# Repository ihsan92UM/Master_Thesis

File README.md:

# Master_Thesis

## Repository Structure
```
Master_Thesis/
├── graphics/
│   └── Contains all .png images used in markdown files
├── pcb_design_files/
│   └── Contains KiCAD 9.0 files 
├── programming_guides/
│   └── Contains programming setup and code import guide
├── stm32c0_codes/
    └── Demo code for funtional board incl. USB, I2C.
```

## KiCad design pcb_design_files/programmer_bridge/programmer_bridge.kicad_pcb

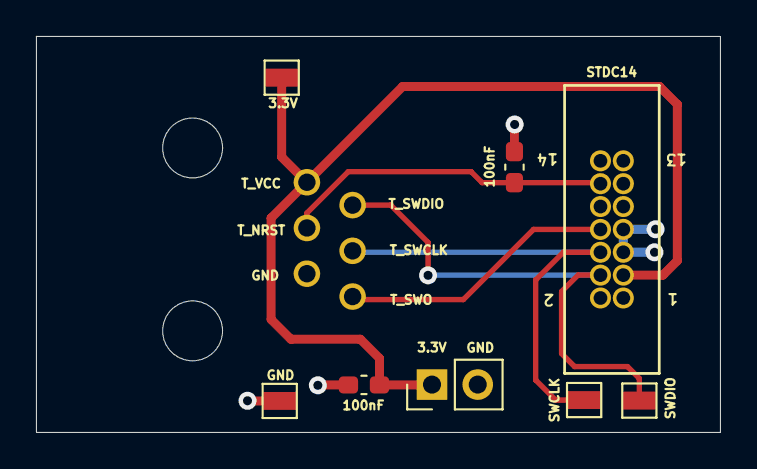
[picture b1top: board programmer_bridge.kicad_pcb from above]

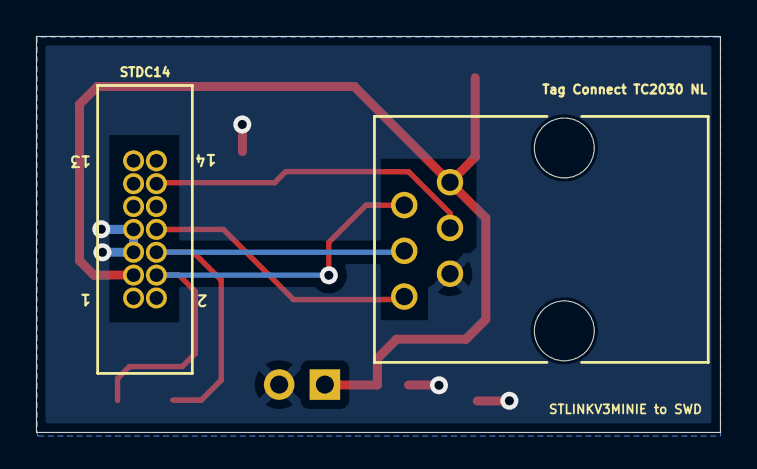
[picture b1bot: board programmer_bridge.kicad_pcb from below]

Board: 2 copper layers, 38.0 x 22.0 mm, 9 parts (2 on the bottom side), 6 nets.

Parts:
C4, C5: 100nF; C_0603_1608Metric_Pad1.08x0.95mm_HandSolder
J1: 5555165-1; CONN6_5555165-1_TEC
J2: 3220-14-0100-00; CONN14_3220-14_CNC
J3: Conn_01x02_Pin; PinHeader_1x02_P2.54mm_Vertical
SWCLK: TestPoint; TestPoint_Pad_1.5x1.5mm
SWDIO: TestPoint; TestPoint_Pad_1.5x1.5mm
TP3, TP6: TestPoint; TestPoint_Pad_1.5x1.5mm

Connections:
/GND: C4.2, C5.2, J1.2, J2.5, J2.7, J3.2, TP3.1
/T_NRST: C5.1, J1.4, J2.12
/T_SWCLK: J1.3, J2.6, SWCLK.1
/T_SWDIO: J1.5, J2.4, SWDIO.1
/T_SWO: J1.1, J2.8
/T_VCC: C4.1, J1.6, J2.3, J3.1, TP6.1

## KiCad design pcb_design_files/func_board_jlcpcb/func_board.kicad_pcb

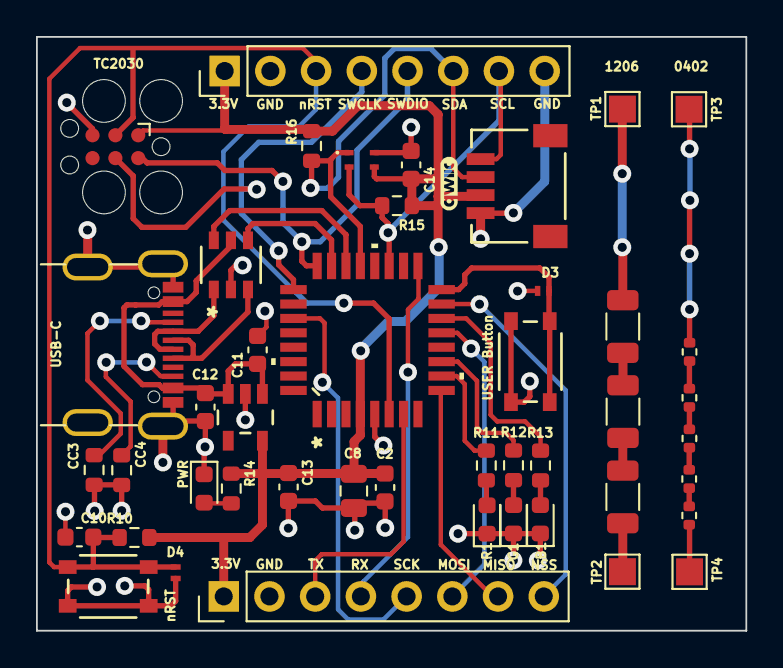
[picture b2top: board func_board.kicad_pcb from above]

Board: 2 copper layers, 39.4 x 33.0 mm, 33 parts (0 on the bottom side), 28 nets.

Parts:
B1: BLUE LED; LED_0603_1608Metric
C2, C10, C11, C14: 100nF; C_0603_1608Metric
C8: 10uF; C_0805_2012Metric
C12, C13: 1uF; C_0603_1608Metric
CC3, CC4: 5K1; R_0603_1608Metric
D3, D4: ESD5Zxx; ESDALC6V1_1M2
G1: GREEN LED; LED_0603_1608Metric
IC2: STS4L-AD1B-R3; STS4LAD1BR3
J6: Conn_ARM_SWD_TagConnect_TC2030; Tag-Connect_TC2030-IDC-FP_2x03_P1.27mm_Vertical
J7: QWIIC-SM04B-SRSS-TB; CONN_SM04B-SRSS-TB_JST
J8, J9: Conn_01x08_Pin; PinHeader_1x08_P2.54mm_Vertical
PWR1: ORANGE LED; LED_0603_1608Metric
R1: RED LED; LED_0603_1608Metric
R10, R15, R16: 4.7K; R_0603_1608Metric
R11, R12, R13, R14: 220R; R_0603_1608Metric
SW3, SW4: Button-TL3365AF180QG; TL3365AF180QG_EWI
U4: STM32C071KBT6; LQFP-32_STM
U5: USBLC6-2SC6Y; SOT23-6L_STM
U6: TPS7A2033PDBVR; DBV0005A-MFG
USB-C1: USB-C-UJ20-C-H-G-SMT-1-P16-TR; SAMESKY_UJ20-C-H-G-SMT-1-P16-TR

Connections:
/DM: U5.1 (I/O1), USB-C1.A7 (DN1), USB-C1.B7 (DN2)
/DP: U5.3 (I/O2), USB-C1.A6 (DP1), USB-C1.B6 (DP2)
/GND: B1.1 (K), C2.2, C8.2, C10.2, C11.2, C12.2, C13.2, C14.2, CC3.2, CC4.2, D3.2 (A), D4.2 (A), G1.1 (K), IC2.4 (VSS), J6.5 (GND), J7.1, J8.2, J8.8, J9.2, PWR1.1 (K), R1.1 (K), SW3.3, SW3.4, SW4.1, SW4.2, U4.5 (VSS/VSSA), U5.2 (GND), U6.2 (GND), USB-C1.A1_B12 (GND), USB-C1.B1_A12 (GND__1), USB-C1.SH1 (SHIELD), USB-C1.SH2 (SHIELD__1), USB-C1.SH3 (SHIELD__2), USB-C1.SH4 (SHIELD__3)
/GPIO1: R11.1, U4.10 (PA3)
/GPIO2: R12.1, U4.11 (PA4)
/GPIO3: R13.1, U4.14 (PA7)
/GPIO4: D3.1 (K), SW4.3, SW4.4, U4.16 (PB1)
/I2C2_SCL: IC2.2 (SCL), J7.4, J8.7, R15.2, U4.19 (PA9)
/I2C2_SDA: IC2.1 (SDA), J7.3, J8.6, R16.2, U4.21 (PA10)
/SPI1_MISO: J9.6, U4.13 (PA6)
/SPI1_MOSI: J9.7, U4.9 (PA2)
/SPI1_NSS: J9.8, U4.15 (PB0)
/SPI1_SCK: J9.5, U4.27 (PB3)
/SWCLK: J6.4 (SWCLK), J8.4, U4.25 (PA14-BOOT0)
/SWDIO: J6.2 (SWDIO), J8.5, U4.24 (PA13)
/USART1_RX: J9.4, U4.17 (PB2)
/USART1_TX: J9.3, U4.7 (PA0)
/USB_DM: U4.22 (PA11[PA9]), U5.6 (I/O1)
/USB_DP: U4.23 (PA12[PA10]), U5.4 (I/O2)
/VBUS: C11.1, C12.1, U5.5 (VBUS), U6.1 (IN), U6.3 (EN), USB-C1.A4_B9 (VBUS), USB-C1.B4_A9 (VBUS__1)
/VDD: C2.1, C8.1, C13.1, C14.1, IC2.3 (VDD), J6.1 (VCC), J7.2, J8.1, J9.1, R10.2, R14.1, R15.1, R16.1, U4.4 (VDD/VDDA), U6.5 (OUT)
/nRESET: C10.1, D4.1 (K), J6.3 (~RESET), J8.3, R10.1, SW3.1, SW3.2, U4.6 (PF2-NRST)
unnamed: PWR1.2 (A), R14.2
unnamed: R1.2 (A), R11.2
unnamed: G1.2 (A), R12.2
unnamed: B1.2 (A), R13.2
unnamed: CC3.1, USB-C1.A5 (CC1)
unnamed: CC4.1, USB-C1.B5 (CC2)

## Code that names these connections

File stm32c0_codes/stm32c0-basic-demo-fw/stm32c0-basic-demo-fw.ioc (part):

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Mcu.Name=STM32C071KBTx
Mcu.Package=LQFP32_GP
Mcu.UserName=STM32C071KBTx
PA10\ [PA12].Mode=I2C
PA10\ [PA12].Signal=I2C1_SDA
PA11\ [PA9].Mode=Device
PA11\ [PA9].Signal=USB_DM
PA12\ [PA10].Mode=Device
PA12\ [PA10].Signal=USB_DP
PA3.GPIOParameters=GPIO_Label
PA3.GPIO_Label=Red LED
PA3.Signal=GPIO_Output
PA4.GPIOParameters=GPIO_Label
PA4.GPIO_Label=Green LED
PA4.Signal=GPIO_Output
PA7.GPIOParameters=GPIO_Label
PA7.GPIO_Label=Blue LED
PA7.Signal=GPIO_Output
PA9\ [PA11].Mode=I2C
PA9\ [PA11].Signal=I2C1_SCL
PB1.GPIOParameters=GPIO_PuPd,GPIO_Label
PB1.GPIO_Label=Button
PB1.GPIO_PuPd=GPIO_PULLUP
PB1.Signal=GPIO_Input
RCC.HSE_VALUE=8000000
RCC.SYSCLKFreq_VALUE=12000000
board=custom

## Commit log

2026-02-25 Correct header formatting in README.md
    Fix formatting of the README header.
2026-06-21 added codes
    added stm32c0 basic functionality code
2026-06-21 programming guide
2026-06-21 added new files
    import code guide, kicad 9.0 files for functional board and programmer bridge
2026-06-21 Fix image paths in STM32CubeIDE import guide
    Updated image paths to use lowercase 'graphics' directory.
2026-06-21 Fix image path for connection diagram in guide
2026-06-21 Update connection diagram image format to PNG
2026-06-21 Expand README with repository structure details
    Added repository structure section with details on contents.
